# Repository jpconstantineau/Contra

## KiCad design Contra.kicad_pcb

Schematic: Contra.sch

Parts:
D1, D2, D3, D4, D5, D6, D7, D8, D9, D10, D11, D12, D13, D14, D15, D16, D17, D18, D19, D20, D21, D22, D23, D24, D25, D26, D27, D28, D29, D30, D31, D32, D33, D34, D35, D36, D37, D38, D39, D40, D41, D42, D43, D44, D45, D46, D47, D48: 1N4148; D_SOD123_axial-dual
J1, J2, J3, J4, J5, J6, J7, J8: Conn_01x01; MountingHole_2.2mm_M2_ISO7380
J9: Conn_01x04; PinHeader_1x04_P2.54mm_Vertical
J10: Conn_01x02; PinHeader_1x02_P2.54mm_Vertical
MX1, MX2, MX3, MX4, MX5, MX6, MX7, MX8, MX9, MX10, MX11, MX12, MX13, MX14, MX15, MX16, MX17, MX18, MX19, MX20, MX21, MX22, MX23, MX24, MX25, MX26, MX27, MX28, MX29, MX30, MX31, MX32, MX33, MX34, MX35, MX36, MX37, MX38, MX39, MX40, MX41, MX42, MX43, MX44, MX45, MX46, MX47, MX48: MX-1U; MX-1U-NoLED
MX49: MX-2U; MX-2U-ReversedStabilizers-NoLED
SW1: SW_PUSH; SW_TACT_ALPS_SKQGABE010
SW2: SW_SPDT; SPDT_C128955
U1: ProMicro; pro_micro

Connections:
+5V: J9.3, U1.21
COL0: MX1.1 (COL), MX13.1 (COL), MX25.1 (COL), MX37.1 (COL), U1.20
COL1: MX2.1 (COL), MX14.1 (COL), MX26.1 (COL), MX38.1 (COL), U1.19
COL2: MX3.1 (COL), MX15.1 (COL), MX27.1 (COL), MX39.1 (COL), U1.12
COL3: MX4.1 (COL), MX16.1 (COL), MX28.1 (COL), MX40.1 (COL), U1.11
COL4: MX5.1 (COL), MX17.1 (COL), MX29.1 (COL), MX41.1 (COL), U1.10
COL5: MX6.1 (COL), MX18.1 (COL), MX30.1 (COL), MX42.1 (COL), MX49.1 (COL), U1.9
COL6: MX7.1 (COL), MX19.1 (COL), MX31.1 (COL), MX43.1 (COL), U1.8
COL7: MX8.1 (COL), MX20.1 (COL), MX32.1 (COL), MX44.1 (COL), U1.7
COL8: MX9.1 (COL), MX21.1 (COL), MX33.1 (COL), MX45.1 (COL), U1.6
COL9: MX10.1 (COL), MX22.1 (COL), MX34.1 (COL), MX46.1 (COL), U1.5
COL10: MX11.1 (COL), MX23.1 (COL), MX35.1 (COL), MX47.1 (COL), U1.2
COL11: MX12.1 (COL), MX24.1 (COL), MX36.1 (COL), MX48.1 (COL), U1.1
GND: J9.4, J10.2, SW1.2, U1.3, U1.4, U1.23
unnamed: D1.2, MX1.2 (ROW)
unnamed: D2.2, MX2.2 (ROW)
unnamed: D3.2, MX3.2 (ROW)
unnamed: D4.2, MX4.2 (ROW)
unnamed: D5.2, MX5.2 (ROW)
unnamed: D6.2, MX6.2 (ROW)
unnamed: D7.2, MX7.2 (ROW)
unnamed: D8.2, MX8.2 (ROW)
unnamed: D9.2, MX9.2 (ROW)
unnamed: D10.2, MX10.2 (ROW)
unnamed: D11.2, MX11.2 (ROW)
unnamed: D12.2, MX12.2 (ROW)
unnamed: D13.2, MX13.2 (ROW)
unnamed: D14.2, MX14.2 (ROW)
unnamed: D15.2, MX15.2 (ROW)
unnamed: D16.2, MX16.2 (ROW)
unnamed: D17.2, MX17.2 (ROW)
unnamed: D18.2, MX18.2 (ROW)
unnamed: D19.2, MX19.2 (ROW)
unnamed: D20.2, MX20.2 (ROW)
unnamed: D21.2, MX21.2 (ROW)
unnamed: D22.2, MX22.2 (ROW)
unnamed: D23.2, MX23.2 (ROW)
unnamed: D24.2, MX24.2 (ROW)
unnamed: D25.2, MX25.2 (ROW)
unnamed: D26.2, MX26.2 (ROW)
unnamed: D27.2, MX27.2 (ROW)
unnamed: D28.2, MX28.2 (ROW)
unnamed: D29.2, MX29.2 (ROW)
unnamed: D30.2, MX30.2 (ROW)
unnamed: D31.2, MX31.2 (ROW)
unnamed: D32.2, MX32.2 (ROW)
unnamed: D33.2, MX33.2 (ROW)
unnamed: D34.2, MX34.2 (ROW)
unnamed: D35.2, MX35.2 (ROW)
unnamed: D36.2, MX36.2 (ROW)
unnamed: D37.2, MX37.2 (ROW)
unnamed: D38.2, MX38.2 (ROW)
unnamed: D39.2, MX39.2 (ROW)
unnamed: D40.2, MX40.2 (ROW)
unnamed: D41.2, MX41.2 (ROW)
unnamed: D42.2, MX42.2 (ROW), MX49.2 (ROW)
unnamed: D43.2, MX43.2 (ROW)
unnamed: D44.2, MX44.2 (ROW)
unnamed: D45.2, MX45.2 (ROW)
unnamed: D46.2, MX46.2 (ROW)
unnamed: D47.2, MX47.2 (ROW)
unnamed: D48.2, MX48.2 (ROW)
unnamed: J9.1, U1.17
unnamed: J9.2, U1.16
unnamed: J10.1, SW2.1
unnamed: SW1.1, U1.22
unnamed: SW2.2, U1.24
ROW0: D1.1, D2.1, D3.1, D4.1, D5.1, D6.1, D7.1, D8.1, D9.1, D10.1, D11.1, D12.1, U1.18
ROW1: D13.1, D14.1, D15.1, D16.1, D17.1, D18.1, D19.1, D20.1, D21.1, D22.1, D23.1, D24.1, U1.15
ROW2: D25.1, D26.1, D27.1, D28.1, D29.1, D30.1, D31.1, D32.1, D33.1, D34.1, D35.1, D36.1, U1.14
ROW3: D37.1, D38.1, D39.1, D40.1, D41.1, D42.1, D43.1, D44.1, D45.1, D46.1, D47.1, D48.1, U1.13

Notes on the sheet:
Contra low-cost ortholinear mechanical keyboard
1 1
I forgot
1.something

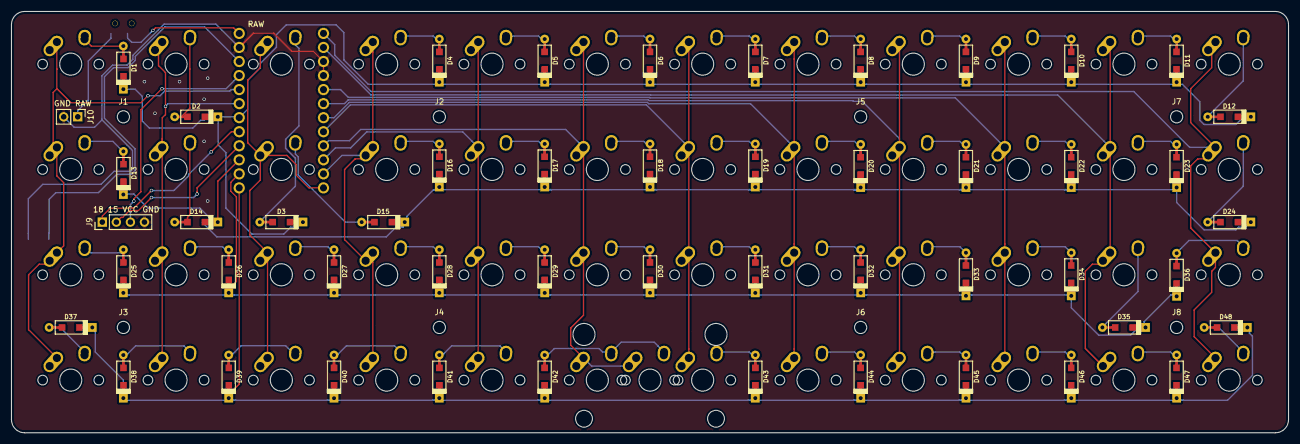
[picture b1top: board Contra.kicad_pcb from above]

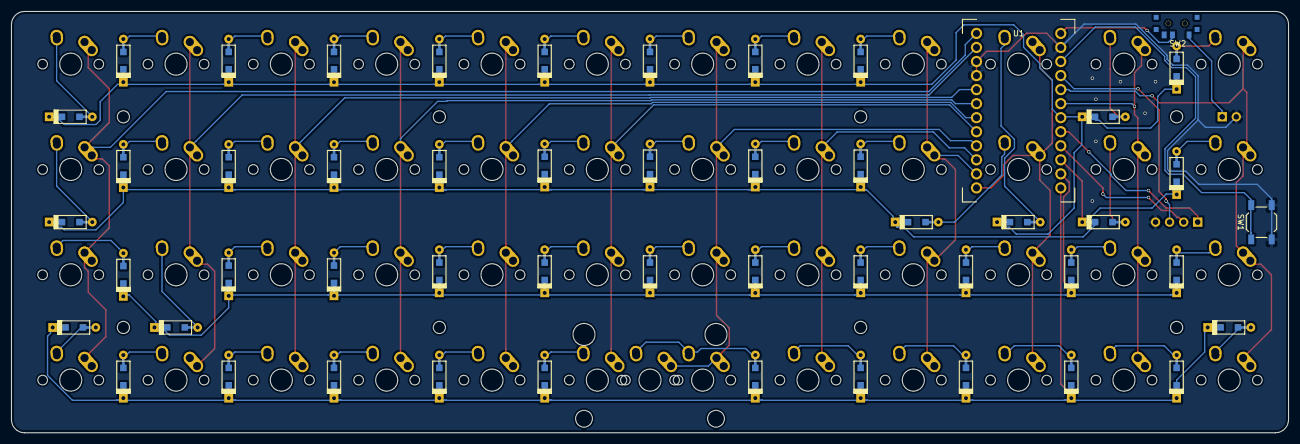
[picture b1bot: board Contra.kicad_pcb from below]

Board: 2 copper layers, 231.0 x 76.2 mm, 110 parts (3 on the bottom side), 71 nets.

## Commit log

2019-05-31 initial commit for wireless mods for BlueMicro
2020-06-14 updated position of standoffs
